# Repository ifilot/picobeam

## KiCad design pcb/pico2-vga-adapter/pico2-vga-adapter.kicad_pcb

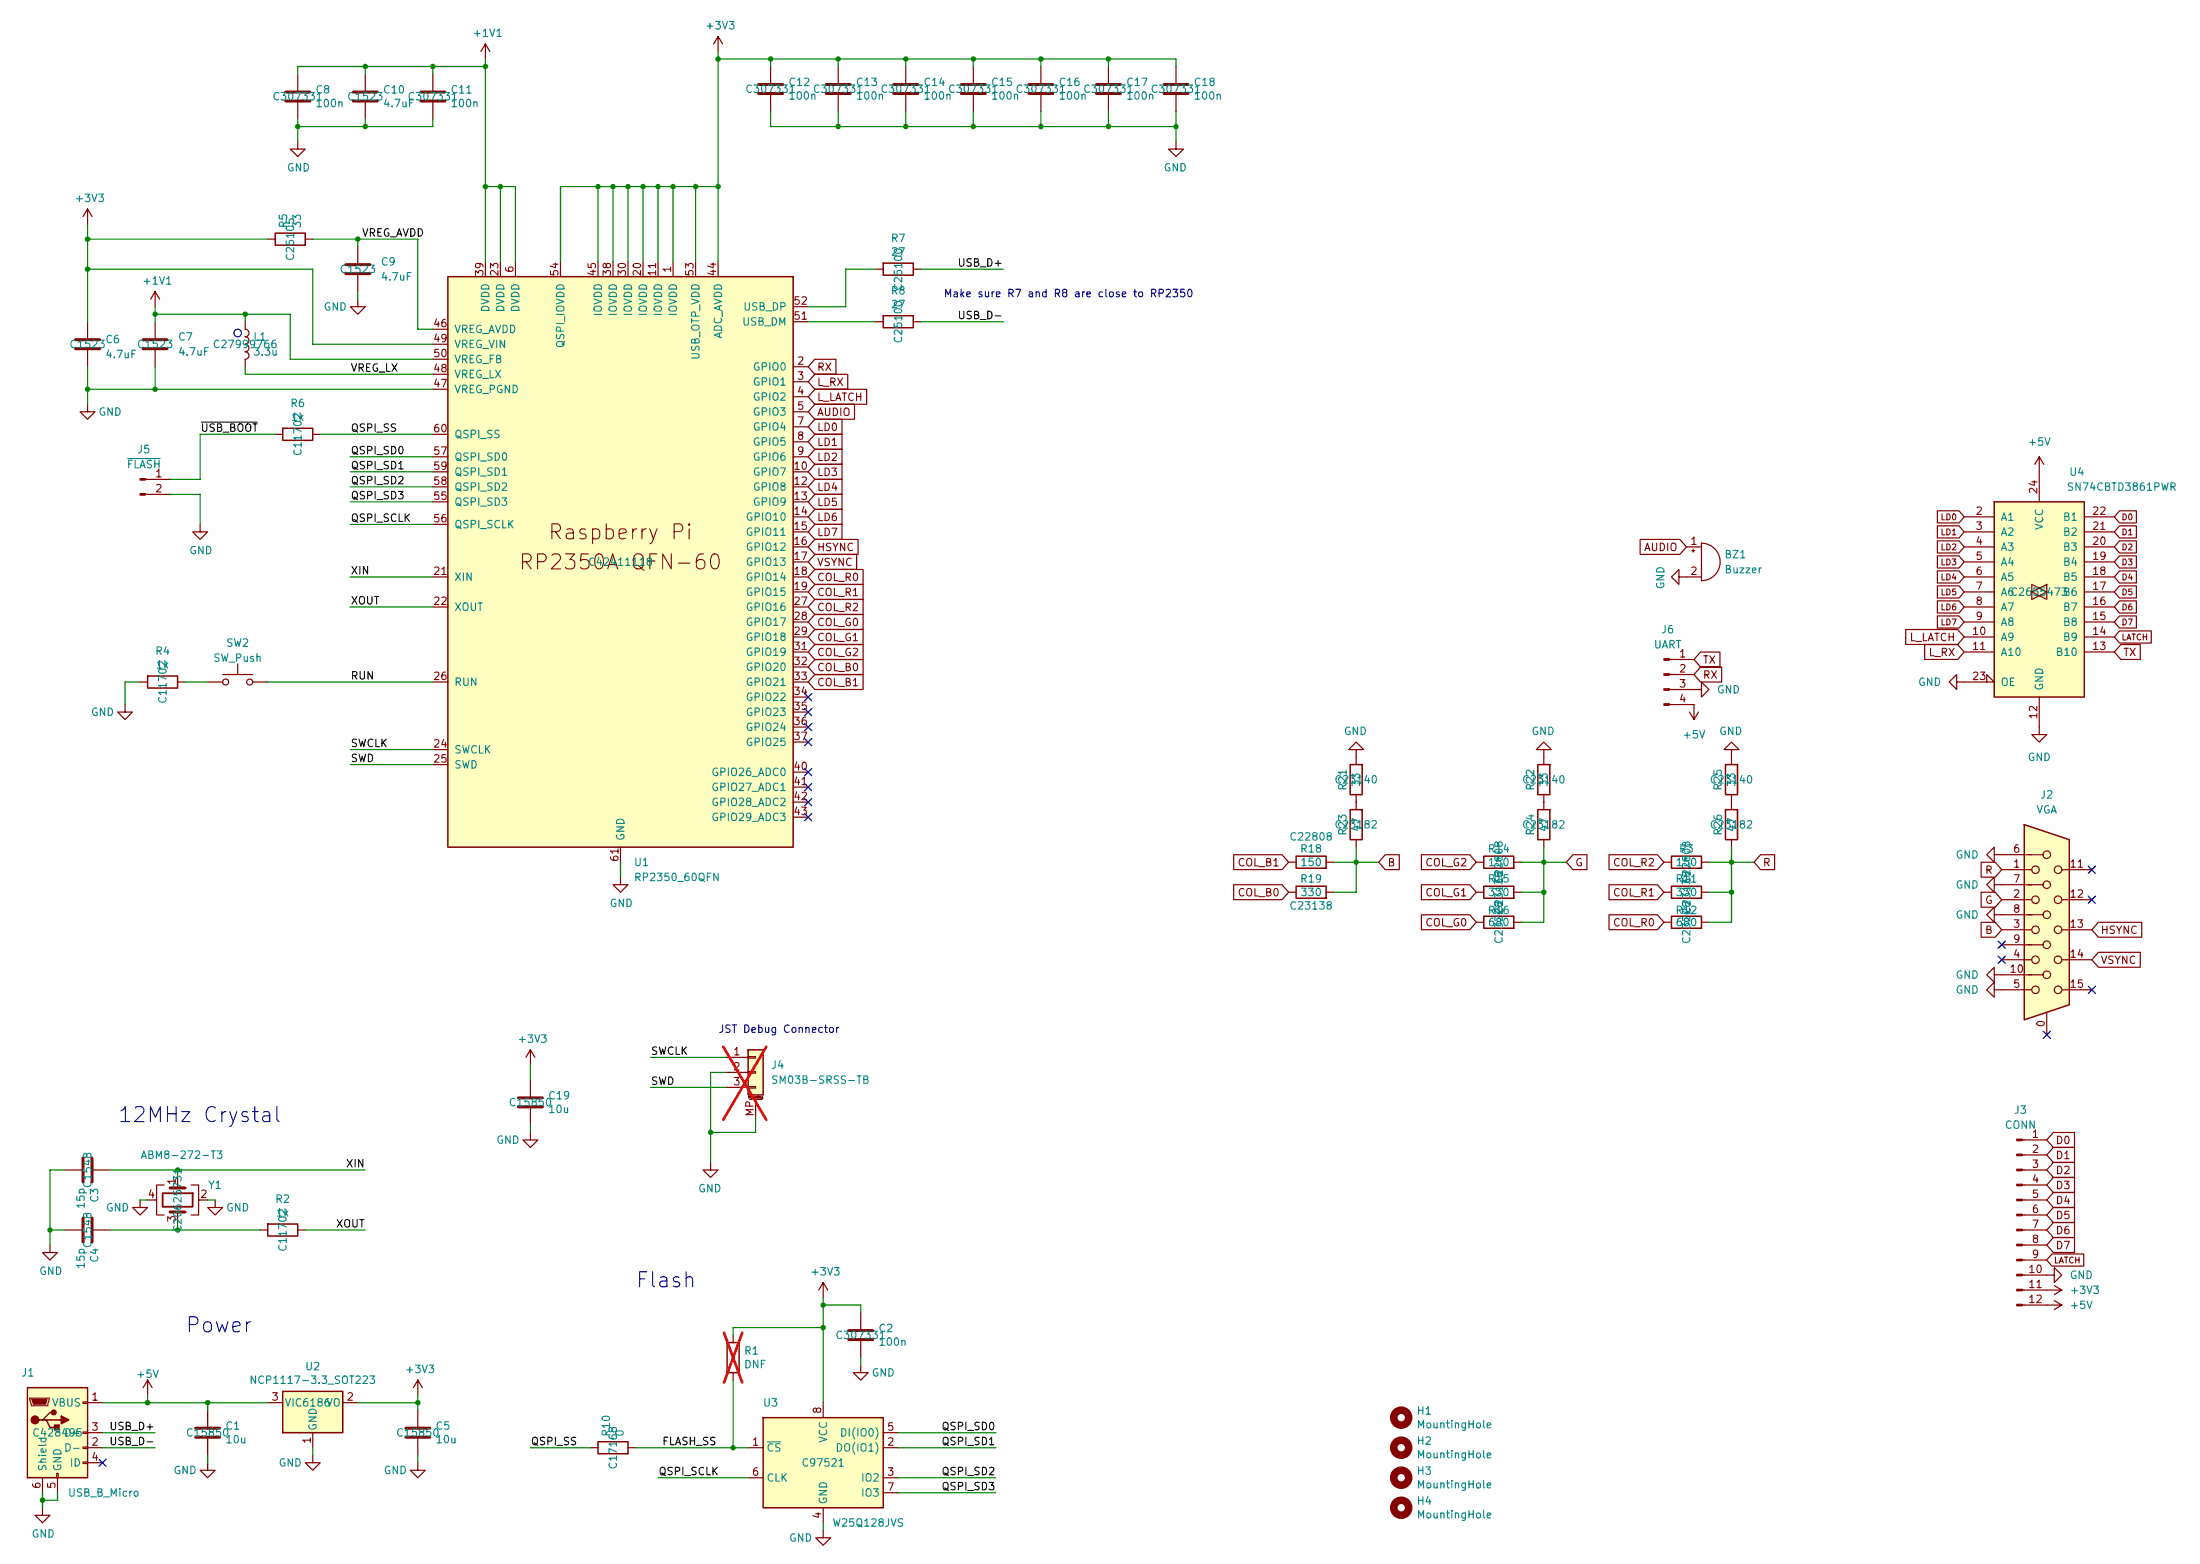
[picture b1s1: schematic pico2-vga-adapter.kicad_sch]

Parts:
BZ1: Buzzer; Buzzer_15x7.5RM7.6
C1, C5, C19: 10u; C_0805_2012Metric; LCSC C15850
C2, C8, C11, C12, C13, C14, C15, C16, C17, C18: 100n; C_0402_1005Metric; LCSC C307331
C3, C4: 15p; C_0402_1005Metric; LCSC C1548
C6, C7: 4.7uF; C_0402_1005Metric_small_pads; LCSC C1523
C9, C10: 4.7uF; C_0402_1005Metric; LCSC C1523
H1, H2, H3, H4: MountingHole; MountingHole_2.7mm_M2.5
J1: USB_B_Micro; USB_Micro-B_Amphenol_10103594-0001LF_Horizontal; LCSC C428495
J2: VGA; 618015330923
J3: CONN; PinHeader_1x12_P2.54mm_Vertical
J4: SM03B-SRSS-TB; JST_SH_SM03B-SRSS-TB_1x03-1MP_P1.00mm_Horizontal; not fitted
J5: ~{FLASH}; PinSocket_1x02_P2.54mm_Vertical
J6: UART; PinHeader_1x04_P2.54mm_Vertical
L1: 3.3u; L_pol_2016; LCSC C27999766
R1: DNF; R_0402_1005Metric; not fitted
R2, R4, R6: 1k; R_0402_1005Metric; LCSC C11702
R3, R14, R18: 150; C_0603_1608Metric; LCSC C22808
R5: 33; R_0402_1005Metric; LCSC C25105
R7, R8: 27; R_0402_1005Metric; LCSC C25100
R10: 0; R_0402_1005Metric; LCSC C17168
R11, R15, R19: 330; C_0603_1608Metric; LCSC C23138
R12, R16: 680; C_0603_1608Metric; LCSC C23228
R21, R22, R25: 33; C_0603_1608Metric; LCSC C23140
R23, R24, R26: 47; C_0603_1608Metric; LCSC C23182
SW2: SW_Push; SW_PUSH_6mm
U1: RP2350_60QFN; RP2350-QFN-60-1EP_7x7_P0.4mm_EP3.4x3.4mm_ThermalVias; LCSC C42411118
U2: NCP1117-3.3_SOT223; SOT-223-3_TabPin2; LCSC C6186
U3: W25Q128JVS; SOIC-8_5.23x5.23mm_P1.27mm; LCSC C97521
U4: SN74CBTD3861PWR; TSSOP-24_4.4x7.8mm_P0.65mm; LCSC C2655473
Y1: ABM8-272-T3; Crystal_SMD_3225-4Pin_3.2x2.5mm; LCSC C20625731

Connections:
+1V1: C7.1, C8.1, C10.1, C11.1, L1.1, U1.6 (DVDD), U1.23 (DVDD), U1.39 (DVDD), U1.50 (VREG_FB)
+3V3: C2.1, C5.1, C6.1, C12.1, C13.1, C14.1, C15.1, C16.1, C17.1, C18.1, C19.1, J3.11, R1.1, R5.1, U1.1 (IOVDD), U1.11 (IOVDD), U1.20 (IOVDD), U1.30 (IOVDD), U1.38 (IOVDD), U1.44 (ADC_AVDD), U1.45 (IOVDD), U1.49 (VREG_VIN), U1.53 (USB_OTP_VDD), U1.54 (QSPI_IOVDD), U2.2 (VO), U3.8 (VCC)
+5V: C1.1, J1.1 (VBUS), J3.12, J6.4, U2.3 (VI), U4.24 (VCC)
/FLASH_SS: R1.2, R10.2, U3.1 (~CS)
/QSPI_SCLK: U1.56 (QSPI_SCLK), U3.6 (CLK)
/QSPI_SD0: U1.57 (QSPI_SD0), U3.5 (DI(IO0))
/QSPI_SD1: U1.59 (QSPI_SD1), U3.2 (DO(IO1))
/QSPI_SD2: U1.58 (QSPI_SD2), U3.3 (IO2)
/QSPI_SD3: U1.55 (QSPI_SD3), U3.7 (IO3)
/QSPI_SS: R6.1, R10.1, U1.60 (QSPI_SS)
/RUN: SW2.2, U1.26 (RUN)
/SWCLK: J4.1, U1.24 (SWCLK)
/SWD: J4.3, U1.25 (SWD)
/USB_D+: J1.3 (D+), R7.1
/USB_D-: J1.2 (D-), R8.1
/VREG_AVDD: C9.1, R5.2, U1.46 (VREG_AVDD)
/VREG_LX: L1.2, U1.48 (VREG_LX)
/XIN: C3.1, U1.21 (XIN), Y1.1
/XOUT: R2.1, U1.22 (XOUT)
/~USB_BOOT: J5.1, R6.2
AUDIO: BZ1.1 (+), U1.5 (GPIO3)
B: J2.3, R18.2, R19.2, R23.1
COL_B0: R19.1, U1.32 (GPIO20)
COL_B1: R18.1, U1.33 (GPIO21)
COL_G0: R16.1, U1.28 (GPIO17)
COL_G1: R15.1, U1.29 (GPIO18)
COL_G2: R14.1, U1.31 (GPIO19)
COL_R0: R12.1, U1.18 (GPIO14)
COL_R1: R11.1, U1.19 (GPIO15)
COL_R2: R3.1, U1.27 (GPIO16)
D0: J3.1, U4.22 (B1)
D1: J3.2, U4.21 (B2)
D2: J3.3, U4.20 (B3)
D3: J3.4, U4.19 (B4)
D4: J3.5, U4.18 (B5)
D5: J3.6, U4.17 (B6)
D6: J3.7, U4.16 (B7)
D7: J3.8, U4.15 (B8)
G: J2.2, R14.2, R15.2, R16.2, R24.1
GND: BZ1.2 (-), C1.2, C2.2, C3.2, C4.2, C5.2, C6.2, C7.2, C8.2, C9.2, C10.2, C11.2, C12.2, C13.2, C14.2, C15.2, C16.2, C17.2, C18.2, C19.2, J1.5 (GND), J1.6 (Shield), J2.5, J2.6, J2.7, J2.8, J2.10, J3.10, J4.2, J4.MP (MountPin), J5.2, J6.3, R4.2, R21.2, R22.2, R25.2, U1.47 (VREG_PGND), U1.61 (GND), U2.1 (GND), U3.4 (GND), U4.12 (GND), U4.23 (OE), Y1.2, Y1.4
HSYNC: J2.13, U1.16 (GPIO12)
LATCH: J3.9, U4.14 (B9)
LD0: U1.7 (GPIO4), U4.2 (A1)
LD1: U1.8 (GPIO5), U4.3 (A2)
LD2: U1.9 (GPIO6), U4.4 (A3)
LD3: U1.10 (GPIO7), U4.5 (A4)
LD4: U1.12 (GPIO8), U4.6 (A5)
LD5: U1.13 (GPIO9), U4.7 (A6)
LD6: U1.14 (GPIO10), U4.8 (A7)
LD7: U1.15 (GPIO11), U4.9 (A8)
L_LATCH: U1.4 (GPIO2), U4.10 (A9)
L_RX: U1.3 (GPIO1), U4.11 (A10)
unnamed: C4.1, R2.2, Y1.3
unnamed: R4.1, SW2.1
unnamed: R21.1, R23.2
unnamed: R22.1, R24.2
unnamed: R25.1, R26.2
unnamed: R8.2, U1.51 (USB_DM)
unnamed: R7.2, U1.52 (USB_DP)
R: J2.1, R3.2, R11.2, R12.2, R26.1
RX: J6.2, U1.2 (GPIO0)
TX: J6.1, U4.13 (B10)
VSYNC: J2.14, U1.17 (GPIO13)

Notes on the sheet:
JST Debug Connector
Flash
Make sure R7 and R8 are close to RP2350
12MHz Crystal
Power

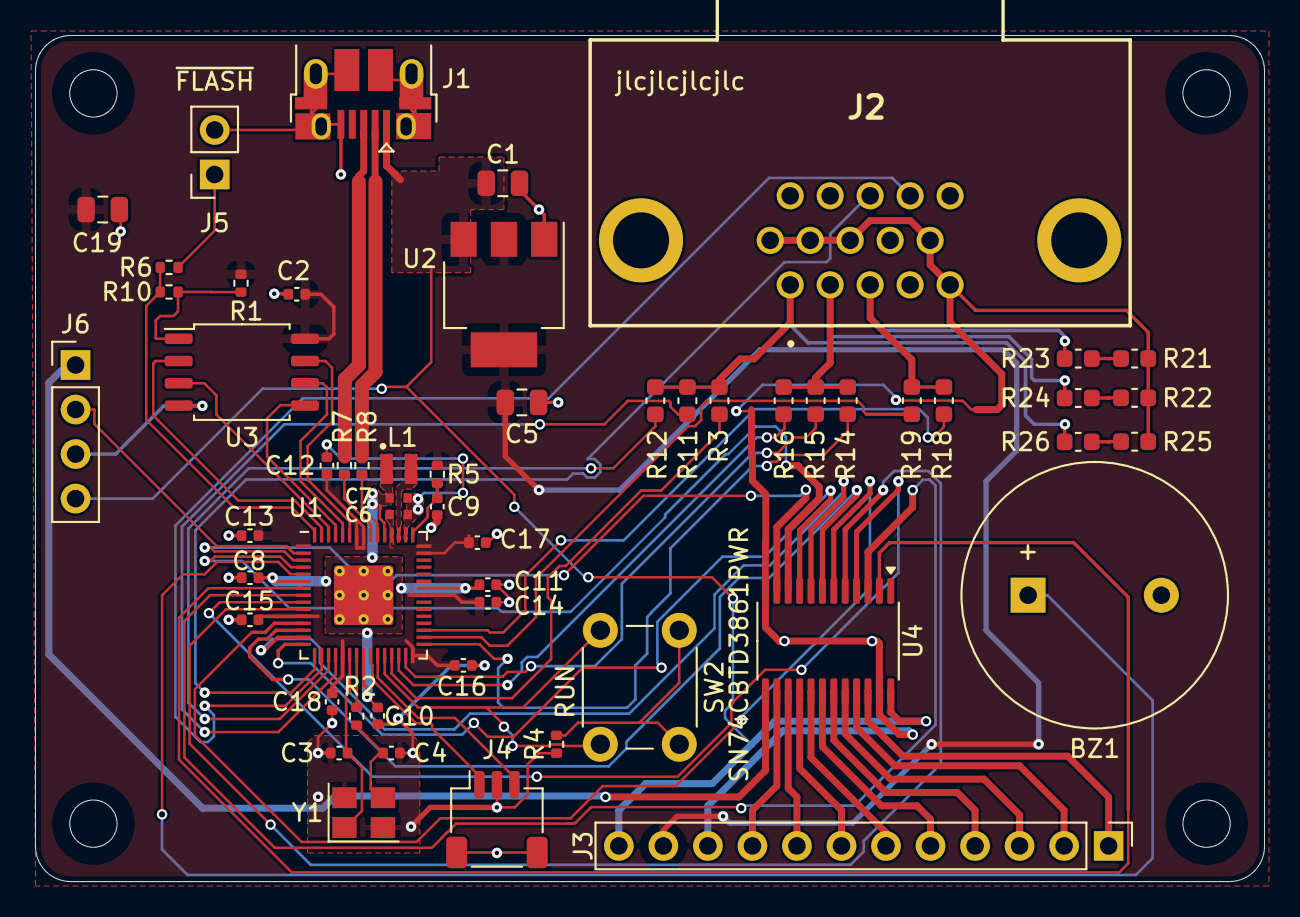
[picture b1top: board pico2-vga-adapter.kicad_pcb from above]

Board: 2 copper layers, 70.1 x 48.3 mm, 59 parts (0 on the bottom side), 63 nets.

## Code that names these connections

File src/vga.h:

/**
 *
 * HARDWARE CONNECTIONS
 *  - GPIO 16 ---> VGA Hsync
 *  - GPIO 17 ---> VGA Vsync
 *  - GPIO 18 ---> 470 ohm resistor ---> VGA Green 
 *  - GPIO 19 ---> 330 ohm resistor ---> VGA Green
 *  - GPIO 20 ---> 330 ohm resistor ---> VGA Blue
 *  - GPIO 21 ---> 330 ohm resistor ---> VGA Red
 *  - RP2040 GND ---> VGA GND
 *
 * RESOURCES USED
 *  - PIO state machines 0, 1, and 2 on PIO instance 0
 *  - DMA channels 0, 1, 2, and 3
 *  - 153.6 kBytes of RAM (for pixel color data)
 *
 */

#ifndef _VGA_H
#define _VGA_H

#include <stdio.h>
#include <stdlib.h>
#include <string.h>
#include <pico/stdlib.h>
#include <hardware/pio.h>
#include <hardware/dma.h>

#include "hsync.pio.h"
#include "vsync.pio.h"
#include "rgb.pio.h"

// Screen width/height
#define SCREENWIDTH     640     // width of the screen
#define SCREENHEIGHT    480     // height of the screen
#define CHARHEIGHT      12      // character width
#define CHARWIDTH        8      // character height

#define LATCH_PIN        2      // GPIO for latch signal
#define HSYNC_PIN       12
#define VSYNC_PIN       13
#define COLOR_PIN       14
#define DATA_BASE_PIN    4        // First data pin

// VGA timing constants
#define H_ACTIVE 655   // (active + frontporch - 1) - one cycle delay for mov
#define V_ACTIVE 479   // (active - 1)
//#define RGB_ACTIVE 319 // (horizontal active)/2 - 1
#define RGB_ACTIVE 639 // change to this if 1 pixel/byte

// Length of the pixel array, and number of DMA transfers
#define TXCOUNT (SCREENWIDTH*SCREENHEIGHT) // Total pixels/2 (since we have 2 pixels per byte)

// Bit masks for drawPixel routine
#define TOPMASK 0b00001111
#define BOTTOMMASK 0b11110000

// For writing text
#define tabspace 4 // number of spaces for a tab

// For accessing the font library
#define pgm_read_byte(addr) (*(const unsigned char *)(addr))

extern bool flag_beep;
extern bool flag_beeping;

extern short cposx;
extern short cposy;
extern short pposx;
extern short pposy;

extern char fg_color;
extern char bg_color;

/**
 * @brief Initialize the screen
 * 
 */
void init_screen(void) ;

/**
 * @brief Clear the screen
 * 
 */
void clear_screen();

/**
 * @brief Draw a single pixel to thes creen buffer
 * 
 * @param x         Pixel x-coordinate
 * @param y         Pixel y-coordinate
 * @param color     Pixel color
 * 
 * 
 * This function modifies the contents of the VGA data array, which is
 * automatically transferred to the screen via a DMA channel.
 */
void draw_pixel(short x, short y, char color) ;

/**
 * @brief Draw a character onto the screen
 * 
 * @param x         Character x-position
 * @param y         Character y-position
 * @param c         Character to print
 * @param color     Foreground color
 * @param bg        Background color
 */
void draw_character(short x, short y, unsigned char c, char color, char bg) ;

void process_pixelword(uint16_t pixelword);

void process_charword(uint16_t pixelword);

#endif // _VGA_H

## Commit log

2025-03-13 Initial commit 8-bit VGA
2025-03-14 Improving API and integrating 8 bit colors
2025-03-16 Designing PCB adapter
2025-03-18 Routing
2025-03-20 Adding components
2025-03-22 Finalizing adapter design
